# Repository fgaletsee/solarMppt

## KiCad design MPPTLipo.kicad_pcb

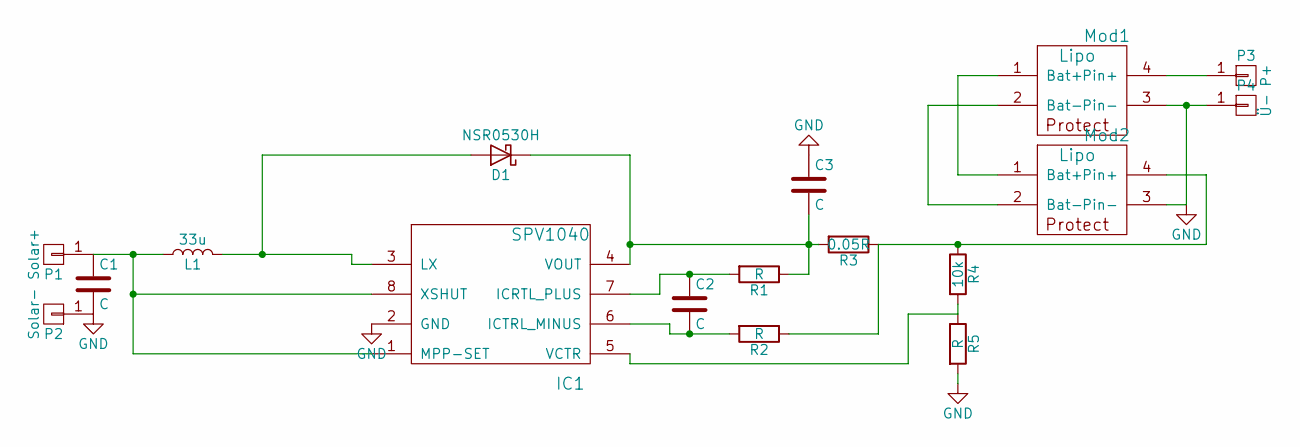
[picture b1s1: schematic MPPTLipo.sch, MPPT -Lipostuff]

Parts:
C1, C2, C3: C; C_0805_HandSoldering
D1: NSR0530H; D_SOD-323_HandSoldering
IC1: SPV1040; TSOT-23-8
L1: 33u; VLS6045EX
Mod1, Mod2: Lipo; LipoProtectPCB
P1: Solar+; Measurement_Point_Square-SMD-Pad_Big
P2: Solar-; Measurement_Point_Square-SMD-Pad_Big
P3: P+; Measurement_Point_Square-SMD-Pad_Big
P4: Ü-; Measurement_Point_Square-SMD-Pad_Big
R1, R2, R5: R; R_0603_HandSoldering
R3: 0.05R; R_0805_HandSoldering
R4: 10k; R_0603_HandSoldering

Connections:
GND: C1.2, C3.1, IC1.2 (GND), Mod1.3 (Pin-), Mod2.3 (Pin-), P2.1, P4.1, R5.2
unnamed: C1.1, IC1.1 (MPP-SET), IC1.8 (XSHUT), L1.1, P1.1
unnamed: C2.1, IC1.7 (ICRTL_PLUS), R1.2
unnamed: C2.2, IC1.6 (ICTRL_MINUS), R2.2
unnamed: C3.2, D1.1 (K), IC1.4 (VOUT), R1.1, R3.2
unnamed: D1.2 (A), IC1.3 (LX), L1.2
unnamed: IC1.5 (VCTR), R4.2, R5.1
unnamed: Mod1.1 (Bat+), Mod2.1 (Bat+)
unnamed: Mod1.2 (Bat-), Mod2.2 (Bat-)
unnamed: Mod1.4 (Pin+), P3.1
unnamed: Mod2.4 (Pin+), R2.1, R3.1, R4.1

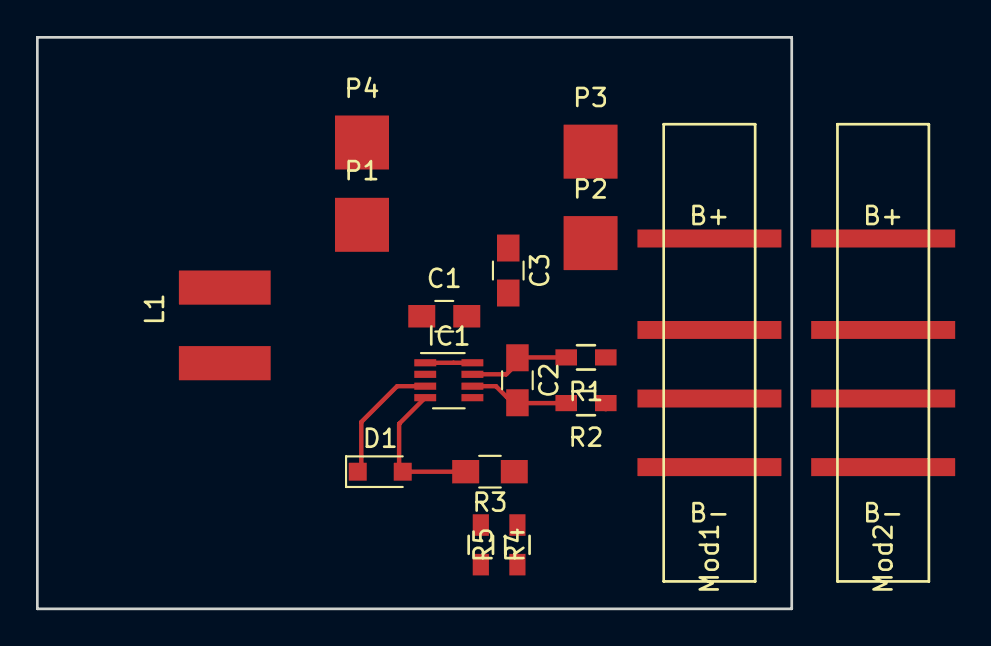
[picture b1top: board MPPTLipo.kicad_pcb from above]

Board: 2 copper layers, 41.9 x 31.8 mm, 17 parts (0 on the bottom side), 11 nets.

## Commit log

2017-02-17 Lipoprotektionsmodul
2017-02-20 Layout fast fertig
